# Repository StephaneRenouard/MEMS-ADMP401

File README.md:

# MEMS-ADMP401
ADMP401 Mems microphone amplifier

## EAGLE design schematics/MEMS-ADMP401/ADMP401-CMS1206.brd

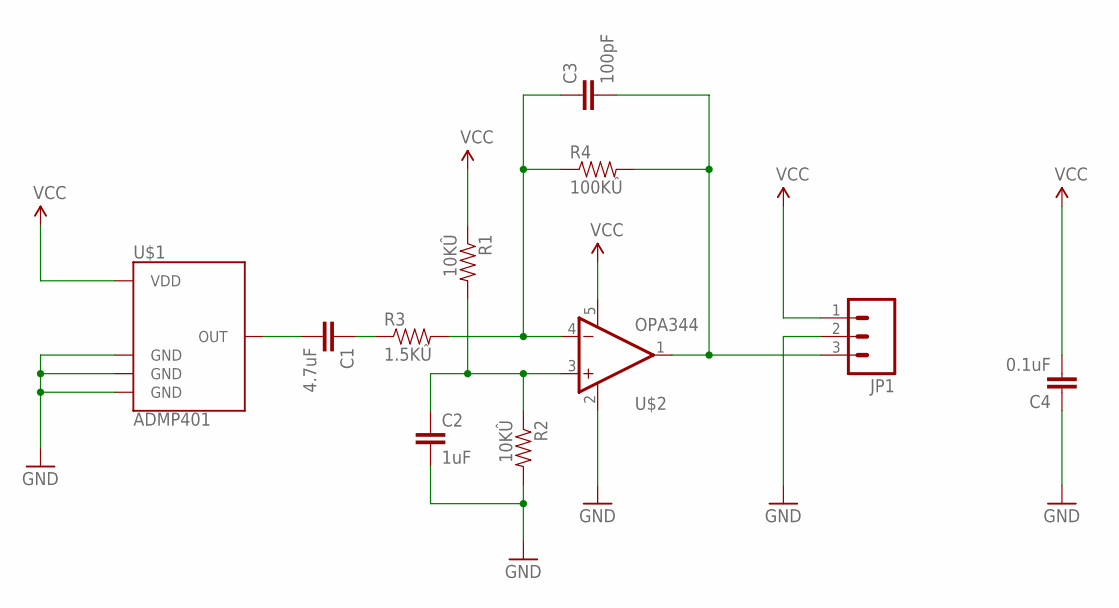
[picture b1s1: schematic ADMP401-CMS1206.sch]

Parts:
C1: 4.7uF; 1206
C2: 1uF; 1206
C3: 100pF; 1206
C4: 0.1uF; 1206
JP1: M03PTH; 1X03
R1, R2: 10KÛ; 1206
R3: 1.5KÛ; 1206
R4: 100KÛ; 1206
U$1: ADMP401
U$2: OPA344; SOT23-5

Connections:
GND: C2.2, C4.1, JP1.2, R2.2, U$1.2 (GND), U$1.4 (GND), U$1.6 (GND), U$2.2 (V-)
unnamed: C1.2, U$1.1 (OUT)
unnamed: C1.1, R3.1
unnamed: C3.1, R3.2, R4.1, U$2.4 (-IN)
unnamed: C3.2, JP1.3, R4.2, U$2.1 (OUT)
unnamed: C2.1, R1.2, R2.1, U$2.3 (+IN)
VCC: C4.2, JP1.1, R1.1, U$1.5 (VDD), U$2.5 (V+)

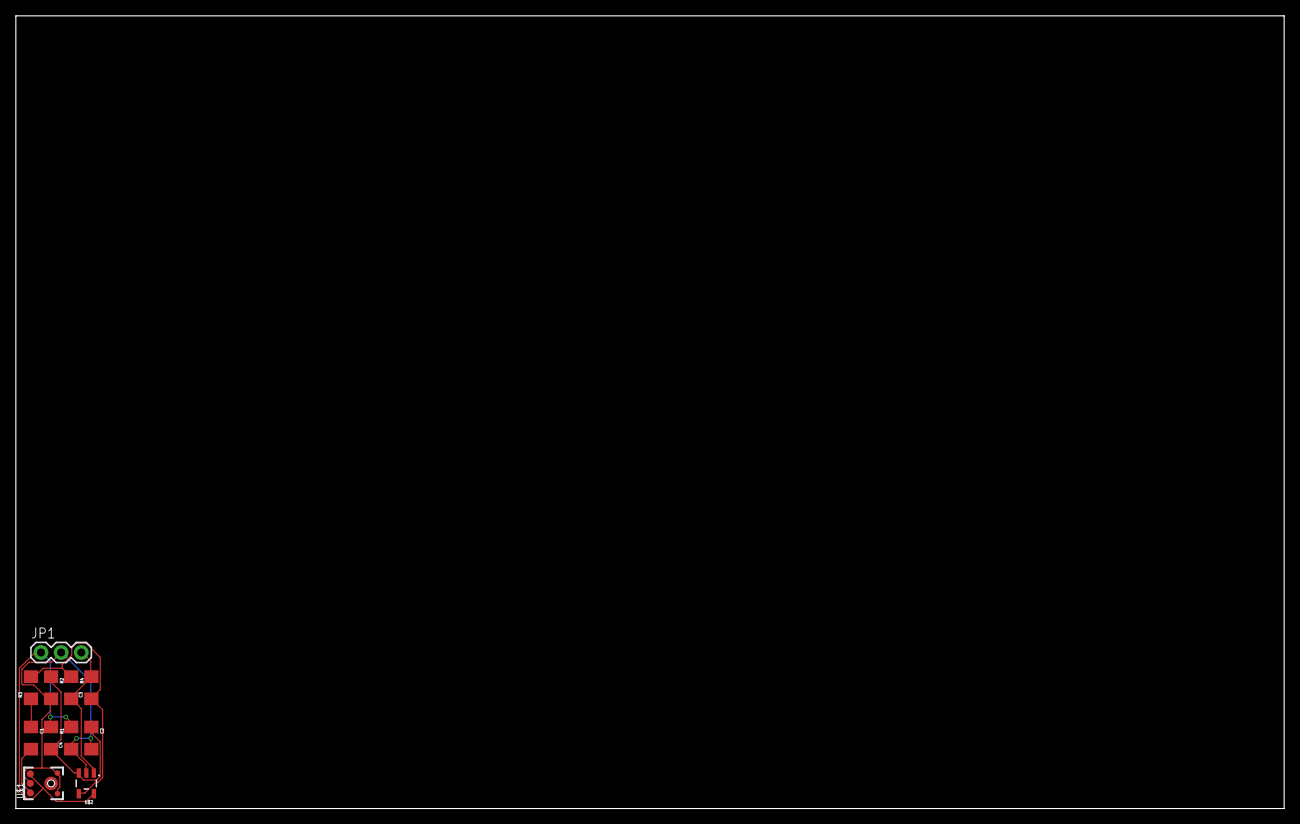
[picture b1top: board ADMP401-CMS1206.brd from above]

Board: 4 copper layers, 160.0 x 100.0 mm, 11 parts (0 on the bottom side), 7 nets.

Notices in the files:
parts and their libraries:
SparkFun-Capacitors: Licensing: Creative Commons ShareAlike 4.0 International - https://creativecommons.org/licenses/by-sa/4.0
